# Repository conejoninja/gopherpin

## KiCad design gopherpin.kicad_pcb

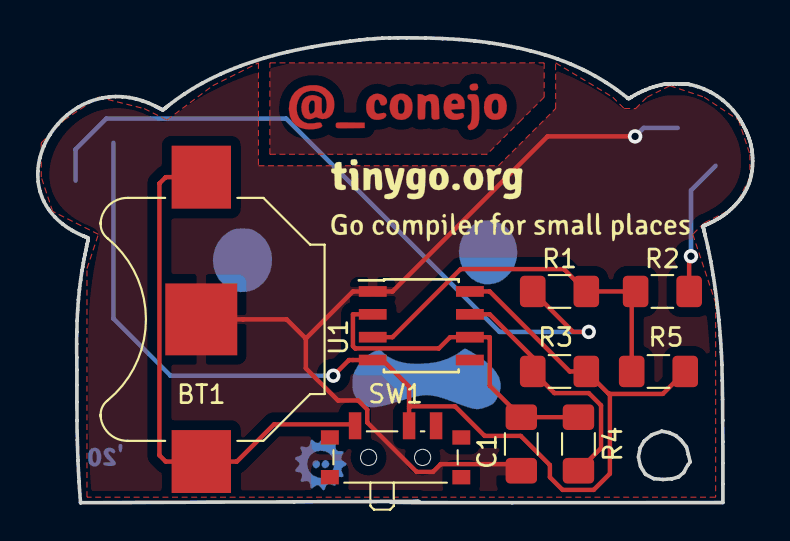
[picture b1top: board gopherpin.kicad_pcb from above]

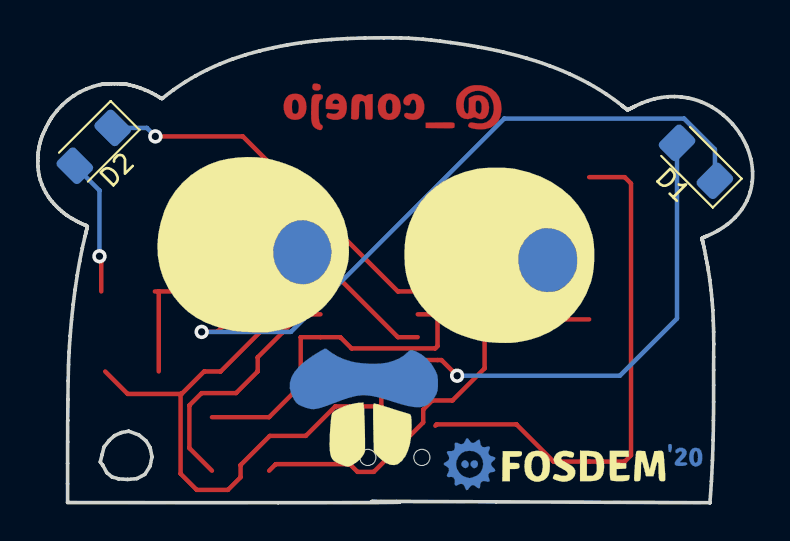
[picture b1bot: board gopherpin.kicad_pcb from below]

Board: 2 copper layers, 39.7 x 25.8 mm, 19 parts (5 on the bottom side), 8 nets.

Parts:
20: LOGO; fosdem_20_cu
20cu: LOGO; fosdem_20_mask
BT1: Battery_Cell; BatteryHolder_Keystone_3000_1x12mm
C1: 10uF; C_1206_3216Metric_Pad1.42x1.75mm_HandSolder
D1, D2: LED; LED_1206_3216Metric_Pad1.42x1.75mm_HandSolder
R1, R2: 68; R_1206_3216Metric_Pad1.42x1.75mm_HandSolder
R3: 10k; R_1206_3216Metric_Pad1.42x1.75mm_HandSolder
R4: 100k; R_1206_3216Metric_Pad1.42x1.75mm_HandSolder
R5: 470; R_1206_3216Metric_Pad1.42x1.75mm_HandSolder
SW1: SW_DPDT_x2; SW_SPDT_PCM12
U1: LM555; SOIC-8_3.9x4.9mm_P1.27mm
conejo: LOGO; conejo
eyes: LOGO; gopher_eyes
fosdem: LOGO; fosdem_20
nose: LOGO; gopher_nose
small_places: LOGO; small_places
tinygo: LOGO; tinygo_org

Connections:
+3V3: D1.2, R3.1, R5.1, SW1.2, U1.4, U1.8
GND: BT1.2, C1.2, D2.1, U1.1
unnamed: BT1.1, SW1.1
unnamed: C1.1, R4.2, U1.2, U1.6
unnamed: D1.1, R1.1
unnamed: D2.2, R2.2
unnamed: R1.2, R2.1, R5.2, U1.3
unnamed: R3.2, R4.1, U1.7

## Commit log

2022-03-07 added v3
